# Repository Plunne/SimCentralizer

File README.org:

#+TITLE: SIMCENTRALIZER
#+AUTHOR: Lena SAVY

A simulation peripherals centralizer, more than a hub.

* TABLE OF CONTENTS :toc:
- [[#code][CODE]]
  - [[#sh6][SH6]]
  - [[#g27][G27]]
- [[#pcb][PCB]]

* CODE

** SH6
Version made for DIY 6 speed Analog axis + 1 Digital reverse shifters.

*Link* : https://github.com/Plunne/SimCentralizer/tree/SH6

** G27

Version made for DIY 6 speed Analog axis + 1 Digital reverse shifters.

*Link* : https://github.com/Plunne/SimCentralizer/tree/G27

* PCB

*Kicad project* : https://github.com/Plunne/SimCentralizer/tree/pcb\\
*GERBER files* : https://github.com/Plunne/SimCentralizer/releases/tag/v1.10

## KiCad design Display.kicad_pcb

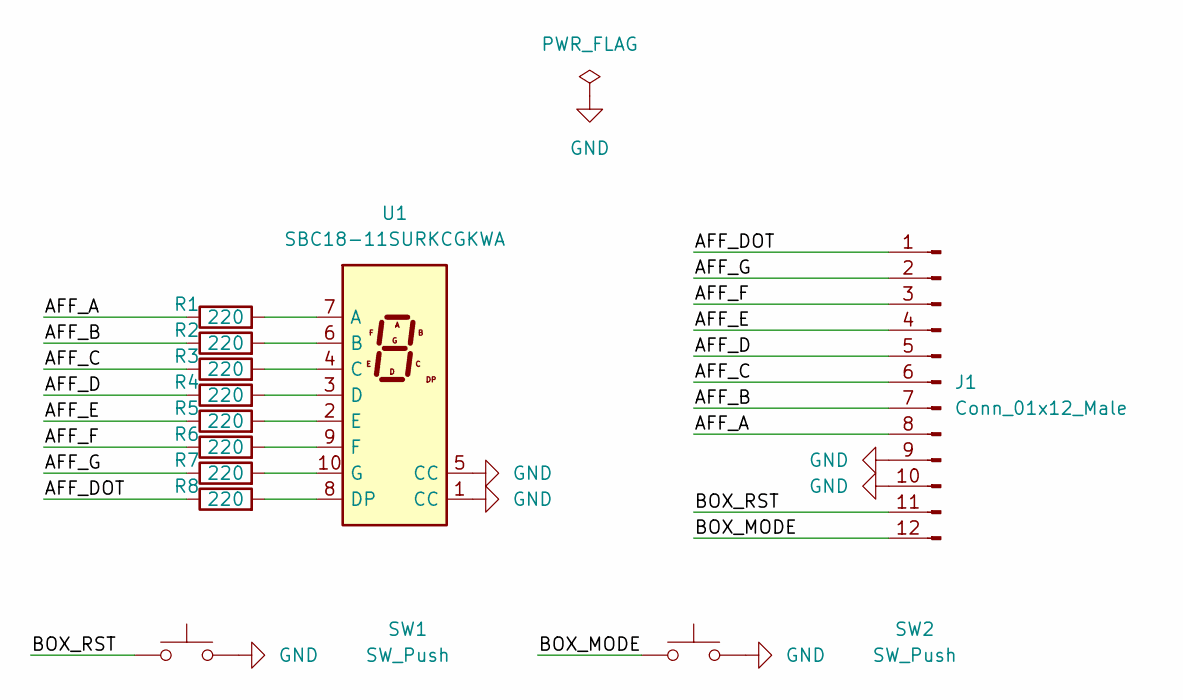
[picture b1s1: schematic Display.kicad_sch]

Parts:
J1: Conn_01x12_Male; PinHeader_1x12_P2.54mm_Vertical
R1, R2, R3, R4, R5, R6, R7, R8: 220; R_1206_3216Metric
SW1, SW2: SW_Push; SW_PUSH_6mm
U1: SBC18-11SURKCGKWA

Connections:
/AFF_A: J1.8, R1.1
/AFF_B: J1.7, R2.1
/AFF_C: J1.6, R3.1
/AFF_D: J1.5, R4.1
/AFF_DOT: J1.1, R8.1
/AFF_E: J1.4, R5.1
/AFF_F: J1.3, R6.1
/AFF_G: J1.2, R7.1
/BOX_MODE: J1.12, SW2.1
/BOX_RST: J1.11, SW1.1
GND: J1.9, J1.10, SW1.2, SW2.2, U1.1 (CC), U1.5 (CC)
unnamed: R1.2, U1.7 (A)
unnamed: R2.2, U1.6 (B)
unnamed: R3.2, U1.4 (C)
unnamed: R4.2, U1.3 (D)
unnamed: R5.2, U1.2 (E)
unnamed: R6.2, U1.9 (F)
unnamed: R7.2, U1.10 (G)
unnamed: R8.2, U1.8 (DP)

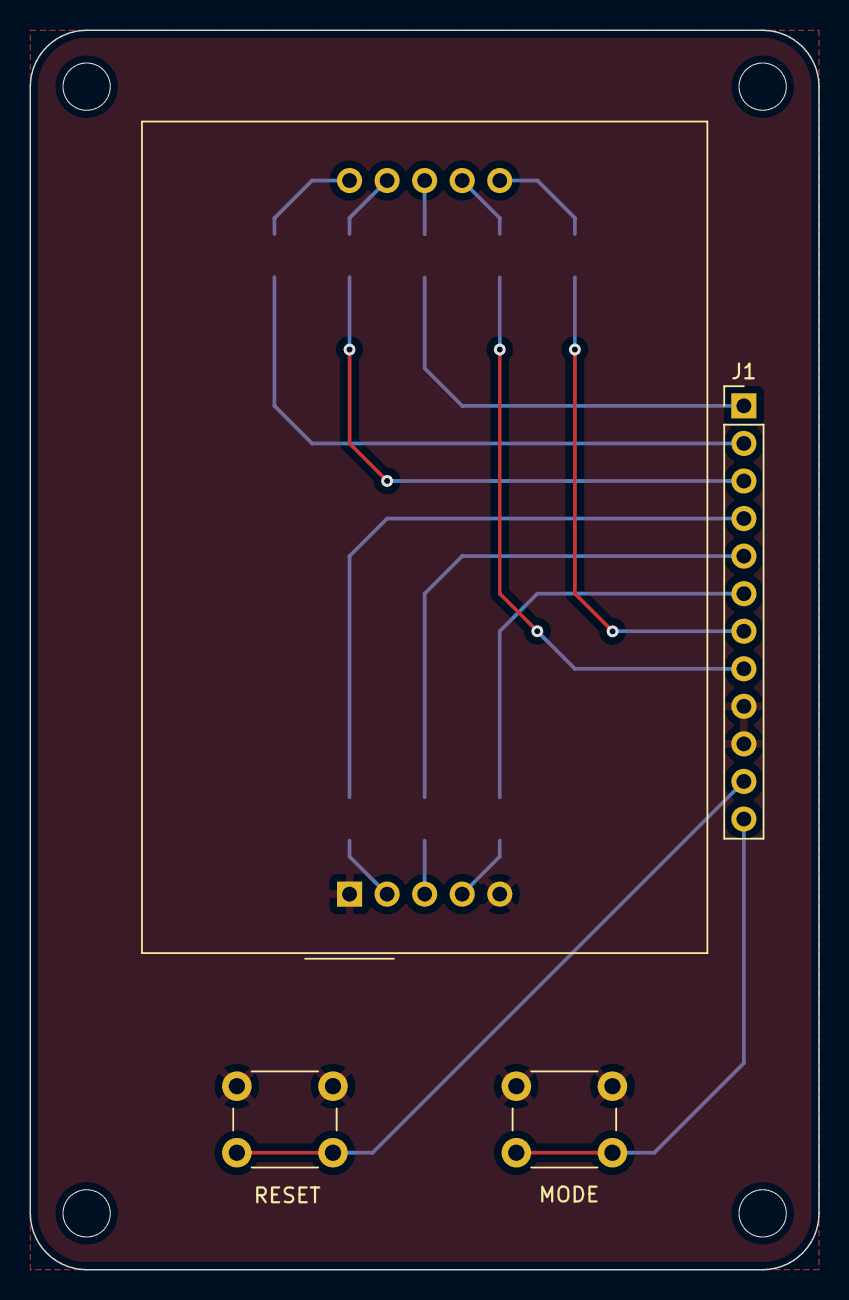
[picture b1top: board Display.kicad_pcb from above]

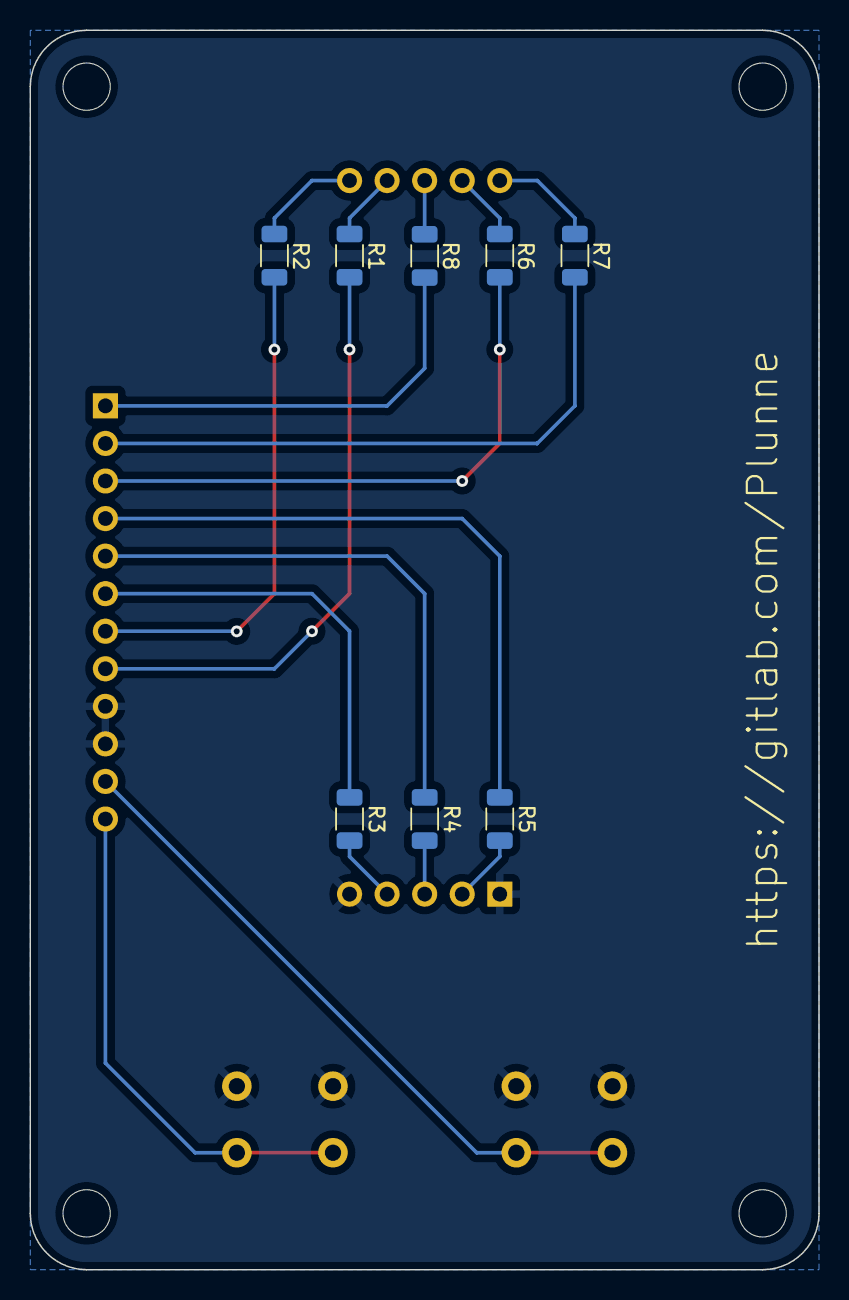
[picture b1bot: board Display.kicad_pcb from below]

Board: 2 copper layers, 53.3 x 83.8 mm, 12 parts (8 on the bottom side), 19 nets.

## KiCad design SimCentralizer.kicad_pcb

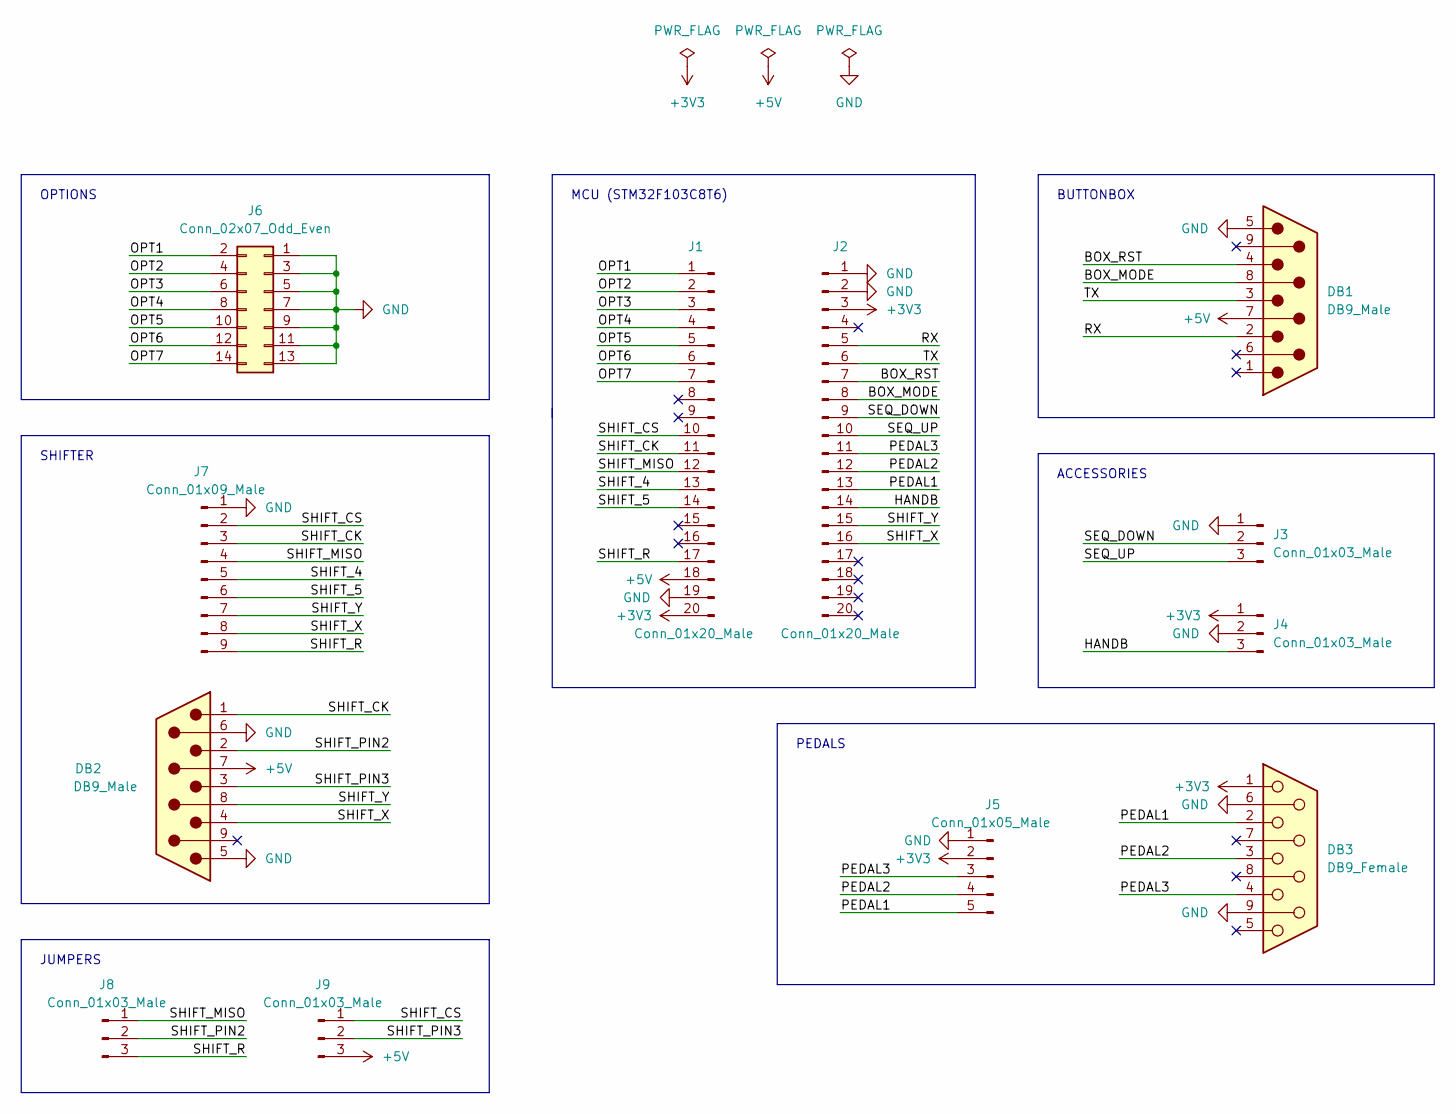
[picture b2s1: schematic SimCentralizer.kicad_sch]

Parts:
DB1, DB2: DB9_Male; DSUB-9_Male_Horizontal_P2.77x2.84mm_EdgePinOffset7.70mm_Hou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
DB3: DB9_Female; DSUB-9_Female_Horizontal_P2.77x2.84mm_EdgePinOffset7.70mm_H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
J1, J2: Conn_01x20_Male; PinHeader_1x20_P2.54mm_Vertical
J3, J4, J8, J9: Conn_01x03_Male; PinHeader_1x03_P2.54mm_Vertical
J5: Conn_01x05_Male; PinHeader_1x05_P2.54mm_Vertical
J6: Conn_02x07_Odd_Even; PinHeader_2x07_P2.54mm_Vertical
J7: Conn_01x09_Male; PinHeader_1x09_P2.54mm_Vertical

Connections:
+3V3: DB3.1, J1.20, J2.3, J4.1, J5.2
+5V: DB1.7, DB2.7, J1.18, J9.3
/BOX_MODE: DB1.8, J2.8
/BOX_RST: DB1.4, J2.7
/HANDB: J2.14, J4.3
/OPT1: J1.1, J6.2
/OPT2: J1.2, J6.4
/OPT3: J1.3, J6.6
/OPT4: J1.4, J6.8
/OPT5: J1.5, J6.10
/OPT6: J1.6, J6.12
/OPT7: J1.7, J6.14
/PEDAL1: DB3.2, J2.13, J5.5
/PEDAL2: DB3.3, J2.12, J5.4
/PEDAL3: DB3.4, J2.11, J5.3
/RX: DB1.2, J2.5
/SEQ_DOWN: J2.9, J3.2
/SEQ_UP: J2.10, J3.3
/SHIFT_4: J1.13, J7.5
/SHIFT_5: J1.14, J7.6
/SHIFT_CK: DB2.1, J1.11, J7.3
/SHIFT_CS: J1.10, J7.2, J9.1
/SHIFT_MISO: J1.12, J7.4, J8.1
/SHIFT_PIN2: DB2.2, J8.2
/SHIFT_PIN3: DB2.3, J9.2
/SHIFT_R: J1.17, J7.9, J8.3
/SHIFT_X: DB2.4, J2.16, J7.8
/SHIFT_Y: DB2.8, J2.15, J7.7
/TX: DB1.3, J2.6
GND: DB1.5, DB2.5, DB2.6, DB3.6, DB3.9, J1.19, J2.1, J2.2, J3.1, J4.2, J5.1, J6.1, J6.3, J6.5, J6.7, J6.9, J6.11, J6.13, J7.1

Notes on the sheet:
OPTIONS
MCU (STM32F103C8T6)
PEDALS
JUMPERS
ACCESSORIES
SHIFTER
BUTTONBOX

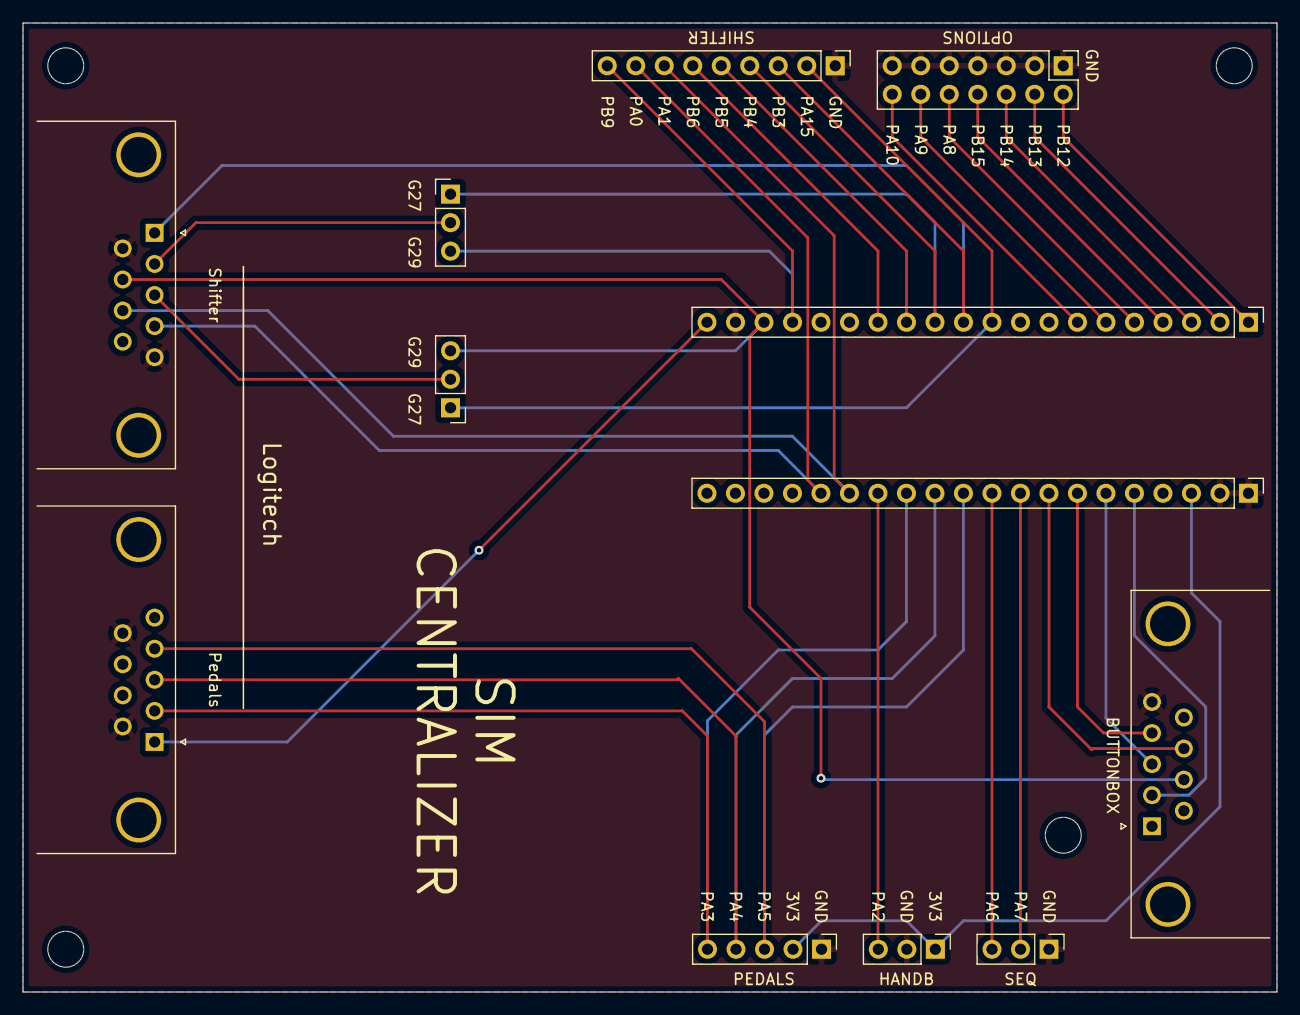
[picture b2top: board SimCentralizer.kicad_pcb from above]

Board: 2 copper layers, 111.8 x 86.4 mm, 12 parts (0 on the bottom side), 30 nets.

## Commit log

2022-08-04 Init SimCentralizer
2022-08-04 Init PCB branch
2022-08-04 README : main
2022-08-06 .gitignore : gerber/
2022-08-06 New branches -> Motherboard/Display
2022-08-06 PCB : Display branch
2022-08-06 PCB : Motherboard branch
2022-08-06 Motherboard : .gitingnore GERBER
2022-08-06 Display : .gitignore Display-backups
2022-08-06 G27 : Add .gitignore (Build, .ccls-cache)
2022-08-06 SH6 : Add .gitignore (Build, .ccls-cache)
2022-08-09 Test magit
